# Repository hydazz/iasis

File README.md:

# iasis

Iasis is a five-port USB-C hub for putting Apple Silicon and T2 Macs into DFU mode without the keyboard sequence. A Mac or Linux host runs the restores; Iasis handles the connections, port power and DFU signalling.

The hardware is a prototype.

## Hardware

| Build | Power and connections                                                                        |
| ----- | -------------------------------------------------------------------------------------------- |
| Hub   | Host USB power for the hub, controls and restores from charged targets                       |
| HubPD | Adds a USB-C power input and per-port charging supplies; works as Hub without a power supply |

The optional [CM5 carrier](hardware/boards/cm5/README.md) plugs into HubPD and houses a Compute Module 5, NVMe storage and Ethernet. Both builds fit the [printed case](hardware/case/README.md), with plain or OLED lids.

See the [main board](hardware/boards/iasis/README.md) for fabrication files and ordering settings.

## Build

Install [mise](https://mise.jdx.dev/) and, for hardware work, KiCad 10 with its standard libraries. Run from the repository root:

```sh
mise install
mise run deps
mise run host:build
```

The CLI is `target/release/iasis` and runs on macOS and Linux. Linux needs read/write access to the management USB device.

| Task               | Output                                                      |
| ------------------ | ----------------------------------------------------------- |
| `mise run build`   | CLI, firmware, case STLs, board STEPs and fabrication files |
| `mise run lint`    | Rust, Python, workflow and KiCad checks                     |
| `mise run test`    | Software, placement-conversion and case-fit tests           |
| `mise run preview` | Board and case images                                       |
| `mise run format`  | Formatted sources and configuration                         |

Builds, checks and previews are separate tasks. Python tools share the root `.venv`; `mise install` also installs the Lefthook hooks.

## Use

Connect the host and charged targets. Ports are numbered 1–5, starting at the dot on the case.

```sh
target/release/iasis list
target/release/iasis --serial 0123456789abcdef status
target/release/iasis --serial 0123456789abcdef dfu 1
target/release/iasis --serial 0123456789abcdef ports --watch
```

Use the serial reported by `list`. Wait for a port to reach `Ready` or `Contract` before sending DFU or reboot. `ports --watch` shows USB enumeration and device identity. Add `--device t2` to `dfu` for a T2 Mac.

| Button gesture        | Action on ready ports                   |
| --------------------- | --------------------------------------- |
| Click                 | Apple Silicon DFU                       |
| Hold for 1.2 seconds  | Reboot connected targets                |
| Two clicks, then hold | Request a restore from a listening host |

DFU does not erase a device. You can use the button with Apple Configurator, or run restores with the CLI below. `power <port> off` disables a port; `power <port> on` enables it and retries a fault.

Native USB-C uses the host's advertised current. With a legacy A-to-C connection, set the remaining shared USB allowance, including Iasis and after subtracting other loads:

```sh
target/release/iasis --serial 0123456789abcdef host-budget 1200
```

The [firmware power table](crates/firmware/README.md#port-power) lists the limits.

### Restore

Install [idevicerestore](https://github.com/libimobiledevice/idevicerestore) and its dependencies. Use the system `usbmuxd` service; macOS includes it, while Linux needs it installed and running.

With a local IPSW:

```sh
target/release/iasis ipsw /path/to/UniversalMac.ipsw
target/release/iasis --serial 0123456789abcdef restore /path/to/UniversalMac.ipsw --ports 1,2,3,4,5 --erase
```

**`--erase` erases the selected targets.** To prepare a batch and start it with the button, replace `--ports 1,2,3,4,5` with `--button`. The command waits for a new restore gesture and exits after that batch. Use `--host-ma 1200` to set a legacy host allowance for the batch.

Each target gets its own idevicerestore process, selected by ECID. Logs and working files go under `restores/`, or the directory passed to `--logs`. Allow space for an extracted OS image per worker. Iasis checks the local archive; idevicerestore checks device compatibility and Apple signing.

## Firmware and protocol

[Build, flash and recover the firmware](crates/firmware/README.md) through the same host USB connection. The [protocol README](crates/protocol/README.md) describes the management interface for host applications.

## License

Original code, firmware, CAD, documentation and enclosure files are [Apache-2.0](LICENSE). Third-party assets retain their own licences and notices.

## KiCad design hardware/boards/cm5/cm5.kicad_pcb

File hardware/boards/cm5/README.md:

# CM5 carrier

An optional Raspberry Pi Compute Module 5 carrier for Iasis. It plugs into the main board's HubPD population and carries Ethernet, NVMe storage, an accessory USB-C port and a service USB-C port. The [CM5 case](../../case/README.md#cm5-assembly) holds both boards.

## Parts and power

| Item                      | Requirement or limit                                       |
| ------------------------- | ---------------------------------------------------------- |
| Main board                | HubPD, with its fitted side socket and power feed          |
| Input                     | USB-C PD supply offering 20 V, connected to the main board |
| Storage                   | eMMC on the module, or NVMe for CM5 Lite; no microSD slot  |
| NVMe SSD                  | M-key, 2230 / 2242 / 2280, up to 6 W                       |
| Fan                       | Up to 0.4 A; rated to tolerate 5.19 V                      |
| RTC backup                | Raspberry Pi RTC Battery SC1163, rechargeable ML2020       |
| Accessory USB-C           | 5 V / 1.5 A                                                |
| Carrier power reservation | 35 W including conversion losses and VCONN                 |

The service port is for CM5 provisioning and recovery; power comes through the main board. Set [`PSU_MAX_CURRENT=5000`](https://www.raspberrypi.com/documentation/computers/raspberry-pi.html#PSU_MAX_CURRENT) in the CM5 EEPROM configuration for the accessory USB allowance.

## RTC battery

Connect the battery to J104. To enable charging, add this to `/boot/firmware/config.txt` and reboot:

```ini
dtparam=rtc_bbat_vchg=3000000
```

Use this setting only with the specified rechargeable battery. See [Raspberry Pi's RTC setup](https://www.raspberrypi.com/documentation/computers/raspberry-pi.html#enable-battery-charging) for diagnostics.

## Fabrication

With the [development tools](../../../README.md#build) installed:

```sh
mise run //hardware/boards/cm5:lint
mise run //hardware/boards/cm5:fab
```

`build/boards/cm5/` contains `gerbers.zip`, `bom.csv` and `cpl.csv`. The board is 75.1 × 102 mm and uses the [main board's six-layer ordering settings](../iasis/README.md#jlcpcb-order). Select its accessory and service USB-C connectors (`J401`, `J501`) in the assembly order.

Use `:step` for the populated STEP and `:preview` for `board.png`. The PCB revision is recorded in the KiCad title block; tag Revision A fabrication files as `cm5-rev-a`.

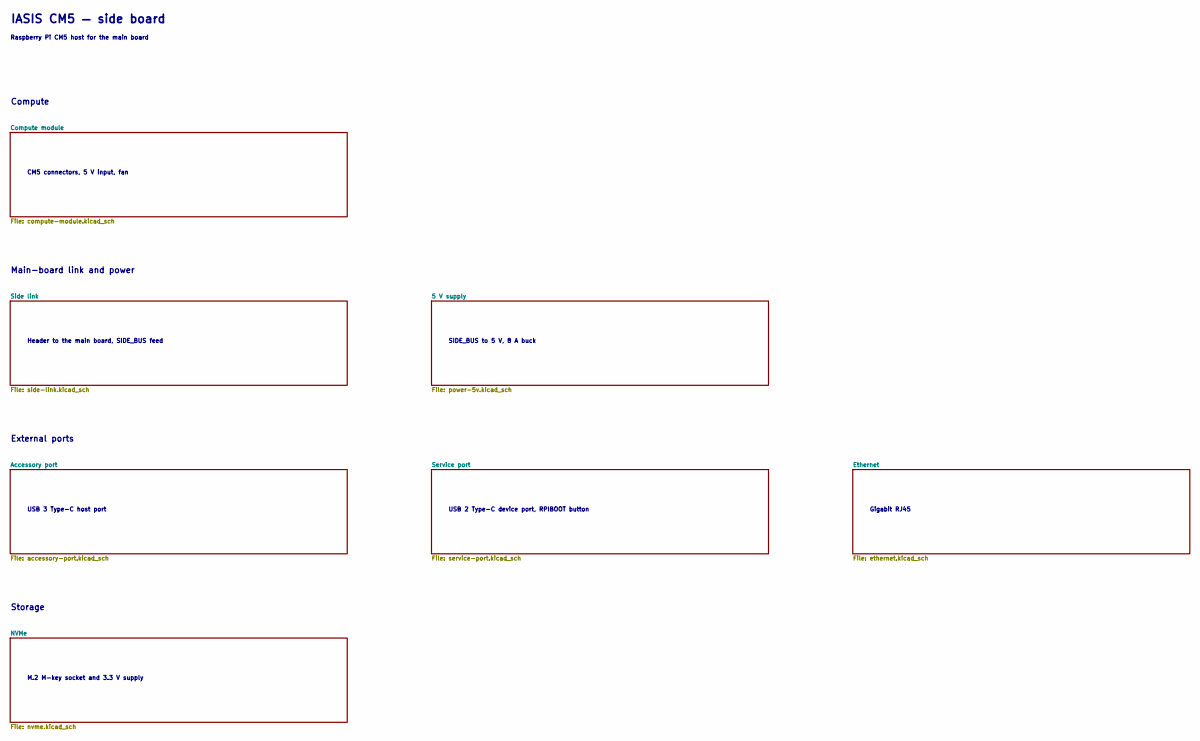
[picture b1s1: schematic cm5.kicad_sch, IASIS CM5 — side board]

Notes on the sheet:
Compute
CM5 connectors, 5 V input, fan
Main-board link and power
Header to the main board, SIDE_BUS feed
SIDE_BUS to 5 V, 8 A buck
External ports
USB 3 Type-C host port
USB 2 Type-C device port, RPIBOOT button
Gigabit RJ45
Storage
M.2 M-key socket and 3.3 V supply
IASIS CM5 — side board
Raspberry Pi CM5 host for the main board

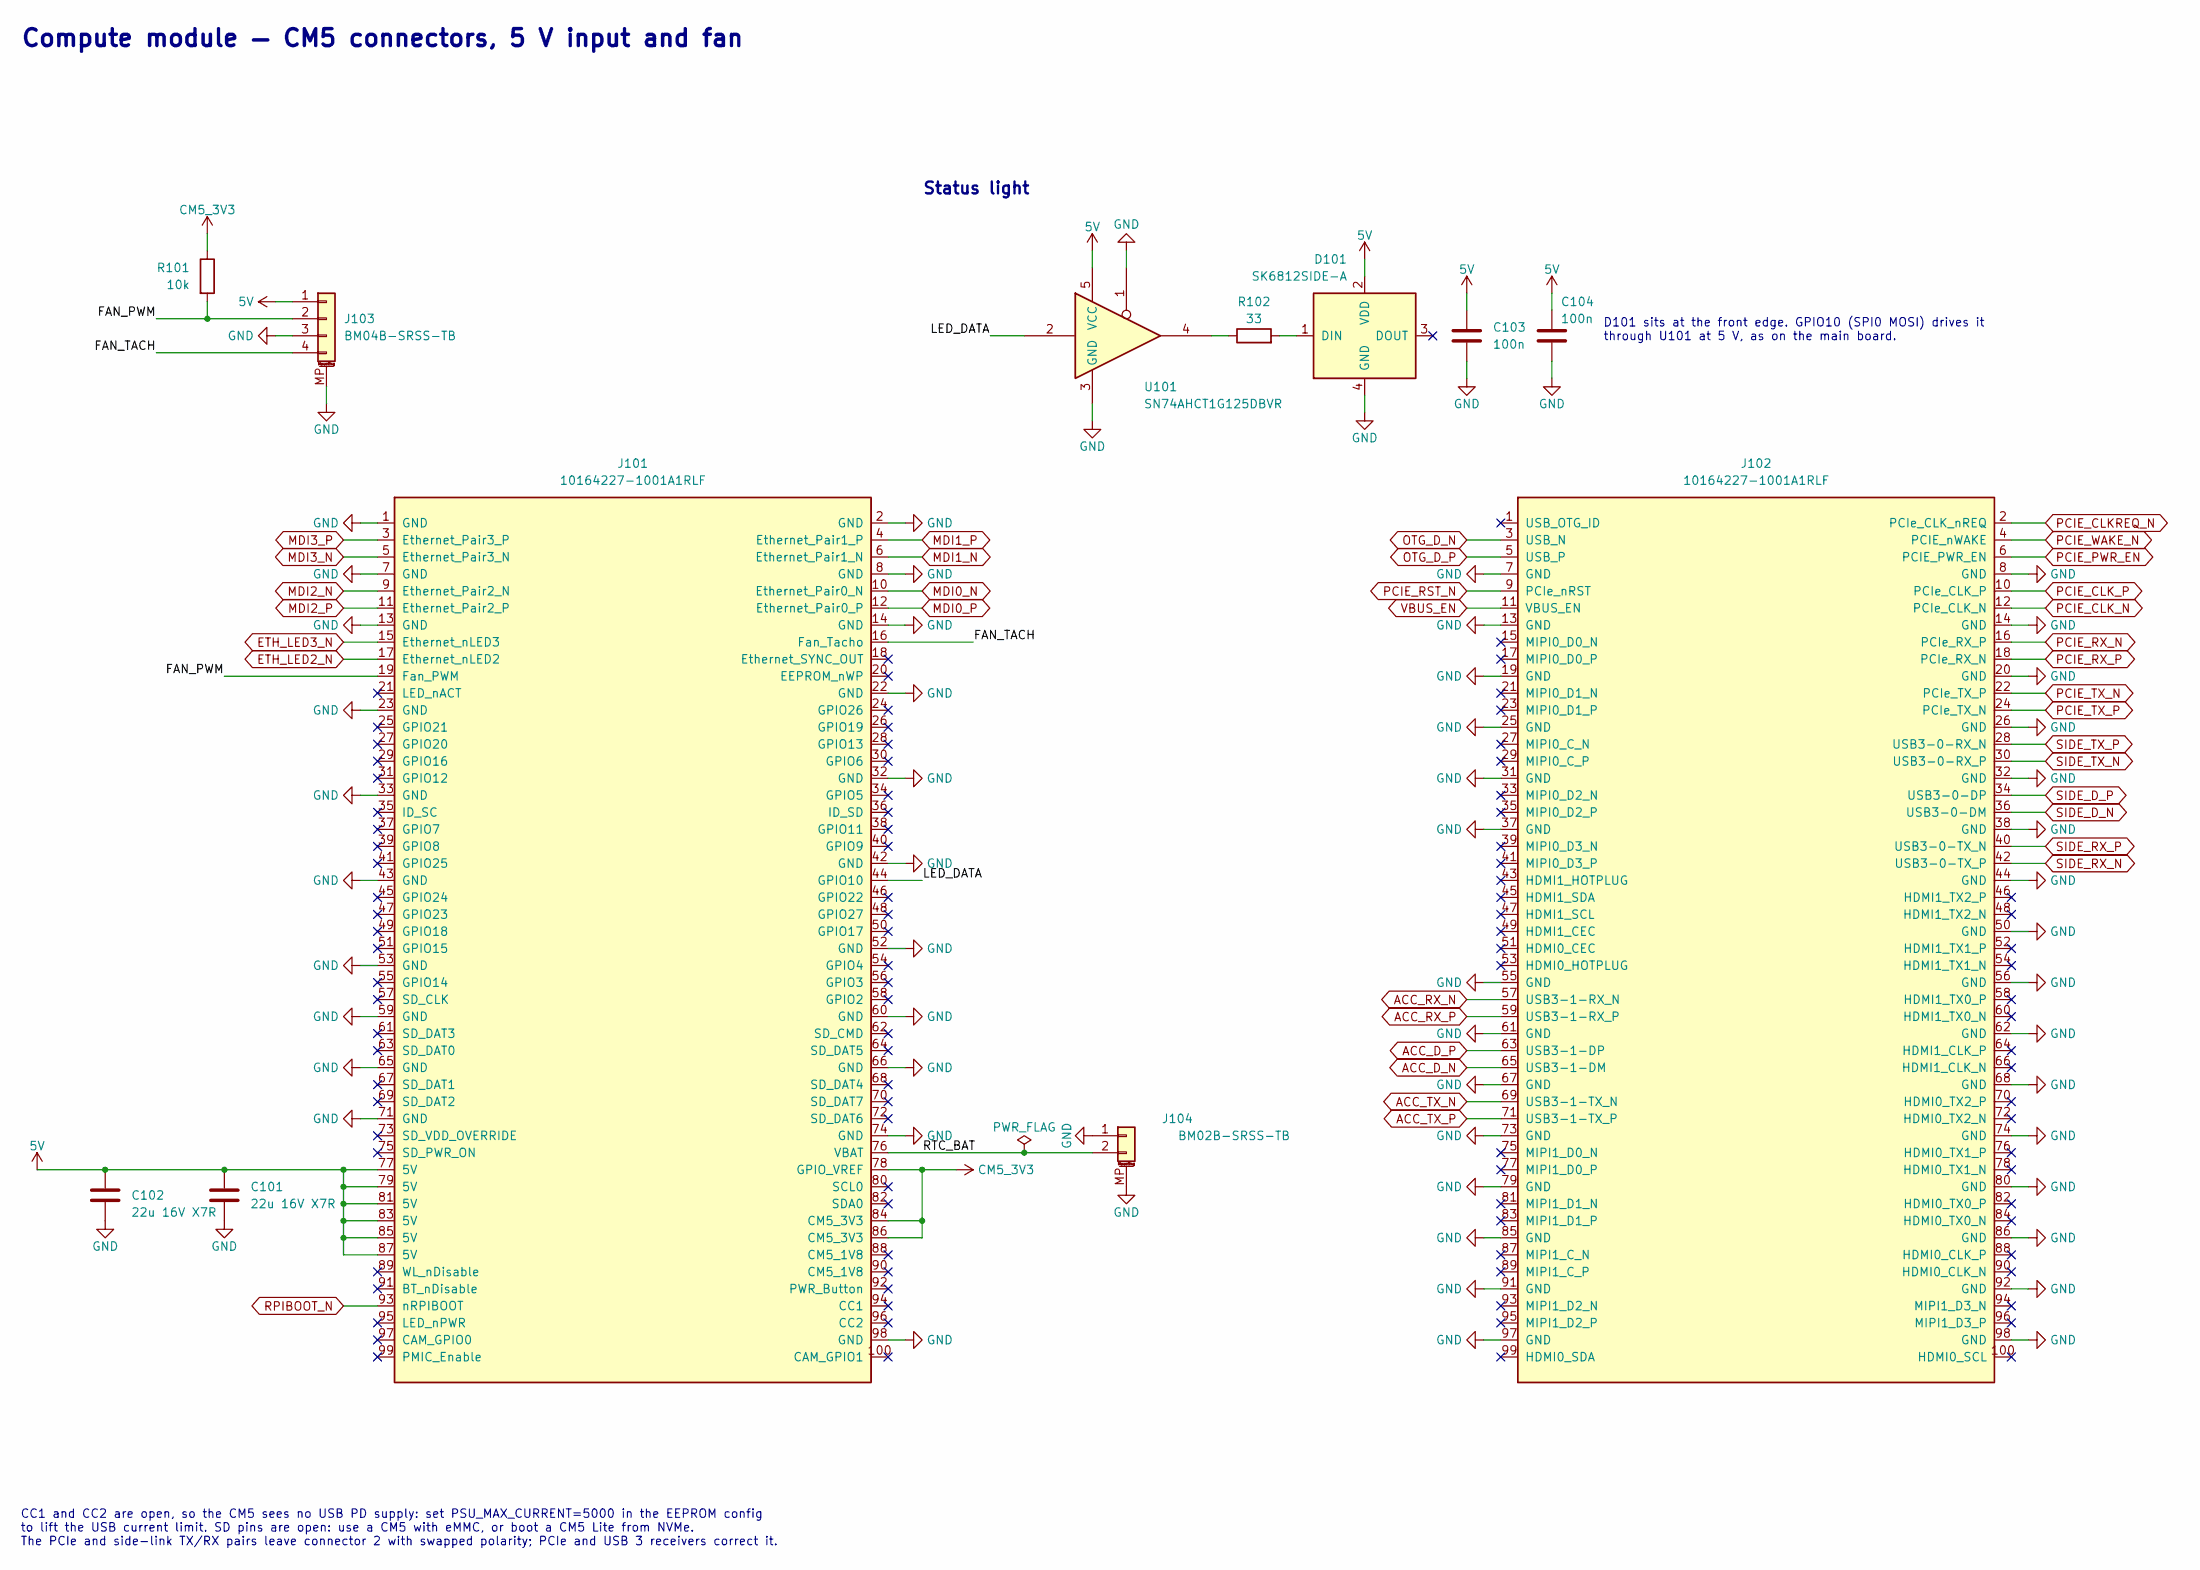
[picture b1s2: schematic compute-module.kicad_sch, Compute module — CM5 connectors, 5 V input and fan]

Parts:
C101, C102: 22u 16V X7R; C_1210_3225Metric; MPN CL32B226KOJNNNE; LCSC C55530
C103, C104: 100n; C_0402_1005Metric; MPN CL05B104KO5NNNC; LCSC C1525
D101: SK6812SIDE-A; OPSCO_SK6812SIDE-A; MPN SK6812SIDE-A; LCSC C5378721
J101, J102: 10164227-1001A1RLF; Hirose_DF40C-100DS-0.4V_2x50_P0.4mm; MPN 10164227-1001A1RLF; LCSC C6782225
J103: BM04B-SRSS-TB; JST_SH_BM04B-SRSS-TB_1x04-1MP_P1.00mm_Vertical; MPN BM04B-SRSS-TB(LF)(SN); LCSC C160390
J104: BM02B-SRSS-TB; JST_SH_BM02B-SRSS-TB_1x02-1MP_P1.00mm_Vertical; MPN BM02B-SRSS-TB(LF)(SN); LCSC C160388
R101: 10k; R_0402_1005Metric; MPN 0402WGF1002TCE; LCSC C25744
R102: 33; R_0402_1005Metric; MPN 0402WGF330JTCE; LCSC C25105
U101: SN74AHCT1G125DBVR; SOT-23-5; MPN SN74AHCT1G125DBVR; LCSC C7484

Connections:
5V: C101.1, C102.1, C103.1, C104.1, D101.2 (VDD), J101.77 (5V), J101.79 (5V), J101.81 (5V), J101.83 (5V), J101.85 (5V), J101.87 (5V), J103.1, U101.5 (VCC); also elsewhere on the board
/Compute module/FAN_PWM: J101.19 (Fan_PWM), J103.2, R101.2
/Compute module/FAN_TACH: J101.16 (Fan_Tacho), J103.4
/Compute module/LED_DATA: J101.44 (GPIO10), U101.2
/Compute module/RTC_BAT: J101.76 (VBAT), J104.2
ACC_D_N: J102.65 (USB3-1-DM); also elsewhere on the board
ACC_D_P: J102.63 (USB3-1-DP); also elsewhere on the board
ACC_RX_N: J102.57 (USB3-1-RX_N); also elsewhere on the board
ACC_RX_P: J102.59 (USB3-1-RX_P); also elsewhere on the board
ACC_TX_N: J102.69 (USB3-1-TX_N); also elsewhere on the board
ACC_TX_P: J102.71 (USB3-1-TX_P); also elsewhere on the board
CM5_3V3: J101.78 (GPIO_VREF), J101.84 (CM5_3V3), J101.86 (CM5_3V3), R101.1; also elsewhere on the board
ETH_LED2_N: J101.17 (Ethernet_nLED2); also elsewhere on the board
ETH_LED3_N: J101.15 (Ethernet_nLED3); also elsewhere on the board
GND: C101.2, C102.2, C103.2, C104.2, D101.4 (GND), J101.1 (GND), J101.2 (GND), J101.7 (GND), J101.8 (GND), J101.13 (GND), J101.14 (GND), J101.22 (GND), J101.23 (GND), J101.32 (GND), J101.33 (GND), J101.42 (GND), J101.43 (GND), J101.52 (GND), J101.53 (GND), J101.59 (GND), J101.60 (GND), J101.65 (GND), J101.66 (GND), J101.71 (GND), J101.74 (GND), J101.98 (GND), J102.7 (GND), J102.8 (GND), J102.13 (GND), J102.14 (GND), J102.19 (GND), J102.20 (GND), J102.25 (GND), J102.26 (GND), J102.31 (GND), J102.32 (GND), J102.37 (GND), J102.38 (GND), J102.44 (GND), J102.50 (GND), J102.55 (GND), J102.56 (GND), J102.61 (GND), J102.62 (GND), J102.67 (GND), J102.68 (GND), J102.73 (GND), J102.74 (GND), J102.79 (GND), J102.80 (GND), J102.85 (GND), J102.86 (GND), J102.91 (GND), J102.92 (GND), J102.97 (GND), J102.98 (GND), J103.3, J103.MP (MountPin), J104.1, J104.MP (MountPin), U101.1, U101.3 (GND); also elsewhere on the board
MDI0_N: J101.10 (Ethernet_Pair0_N); also elsewhere on the board
MDI0_P: J101.12 (Ethernet_Pair0_P); also elsewhere on the board
MDI1_N: J101.6 (Ethernet_Pair1_N); also elsewhere on the board
MDI1_P: J101.4 (Ethernet_Pair1_P); also elsewhere on the board
MDI2_N: J101.9 (Ethernet_Pair2_N); also elsewhere on the board
MDI2_P: J101.11 (Ethernet_Pair2_P); also elsewhere on the board
MDI3_N: J101.5 (Ethernet_Pair3_N); also elsewhere on the board
MDI3_P: J101.3 (Ethernet_Pair3_P); also elsewhere on the board
unnamed: D101.1 (DIN), R102.2
unnamed: R102.1, U101.4
OTG_D_N: J102.3 (USB_N); also elsewhere on the board
OTG_D_P: J102.5 (USB_P); also elsewhere on the board
PCIE_CLKREQ_N: J102.2 (PCIe_CLK_nREQ); also elsewhere on the board
PCIE_CLK_N: J102.12 (PCIe_CLK_N); also elsewhere on the board
PCIE_CLK_P: J102.10 (PCIe_CLK_P); also elsewhere on the board
PCIE_PWR_EN: J102.6 (PCIE_PWR_EN); also elsewhere on the board
PCIE_RST_N: J102.9 (PCIe_nRST); also elsewhere on the board
PCIE_RX_N: J102.16 (PCIe_RX_P); also elsewhere on the board
PCIE_RX_P: J102.18 (PCIe_RX_N); also elsewhere on the board
PCIE_TX_N: J102.22 (PCIe_TX_P); also elsewhere on the board
PCIE_TX_P: J102.24 (PCIe_TX_N); also elsewhere on the board
PCIE_WAKE_N: J102.4 (PCIE_nWAKE); also elsewhere on the board
RPIBOOT_N: J101.93 (nRPIBOOT); also elsewhere on the board
SIDE_D_N: J102.36 (USB3-0-DM); also elsewhere on the board
SIDE_D_P: J102.34 (USB3-0-DP); also elsewhere on the board
SIDE_RX_N: J102.42 (USB3-0-TX_P); also elsewhere on the board
SIDE_RX_P: J102.40 (USB3-0-TX_N); also elsewhere on the board
SIDE_TX_N: J102.30 (USB3-0-RX_P); also elsewhere on the board
SIDE_TX_P: J102.28 (USB3-0-RX_N); also elsewhere on the board
VBUS_EN: J102.11 (VBUS_EN); also elsewhere on the board

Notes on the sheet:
Compute module — CM5 connectors, 5 V input and fan
CC1 and CC2 are open, so the CM5 sees no USB PD supply: set PSU_MAX_CURRENT=5000 in the EEPROM config to lift the USB current limit. SD pins are open: use a CM5 with eMMC, or boot a CM5 Lite from NVMe. The PCIe and side-link TX/RX pairs leave connector 2 with swapped polarity; PCIe and USB 3 receiv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
Status light
D101 sits at the front edge. GPIO10 (SPI0 MOSI) drives it through U101 at 5 V, as on the main board.

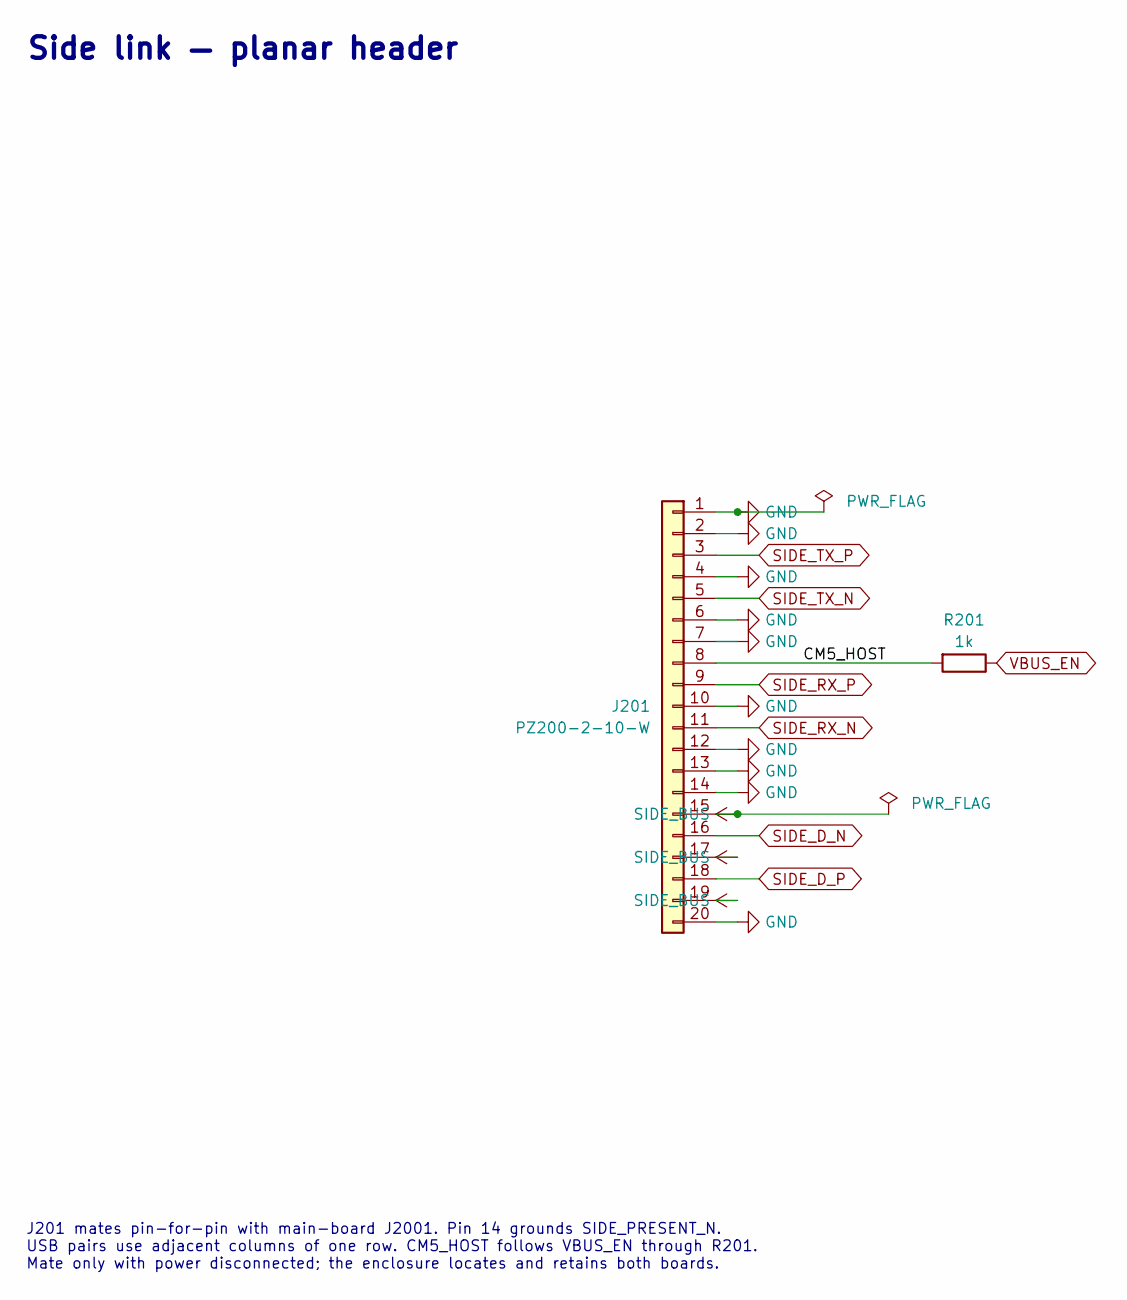
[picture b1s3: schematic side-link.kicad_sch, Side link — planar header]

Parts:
J201: PZ200-2-10-W; PinHeader_2x10_P2.00mm_Horizontal; MPN PZ200-2-10-W; LCSC C2906016
R201: 1k; R_0402_1005Metric; MPN 0402WGF1001TCE; LCSC C11702

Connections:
/Side link/CM5_HOST: J201.8, R201.2
GND: J201.1, J201.2, J201.4, J201.6, J201.7, J201.10, J201.12, J201.13, J201.14, J201.20; also elsewhere on the board
SIDE_BUS: J201.15, J201.17, J201.19; also elsewhere on the board
SIDE_D_N: J201.16; also elsewhere on the board
SIDE_D_P: J201.18; also elsewhere on the board
SIDE_RX_N: J201.11; also elsewhere on the board
SIDE_RX_P: J201.9; also elsewhere on the board
SIDE_TX_N: J201.5; also elsewhere on the board
SIDE_TX_P: J201.3; also elsewhere on the board
VBUS_EN: R201.1; also elsewhere on the board

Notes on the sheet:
Side link — planar header
J201 mates pin-for-pin with main-board J2001. Pin 14 grounds SIDE_PRESENT_N. USB pairs use adjacent columns of one row. CM5_HOST follows VBUS_EN through R201. Mate only with power disconnected; the enclosure locates and retains both boards.

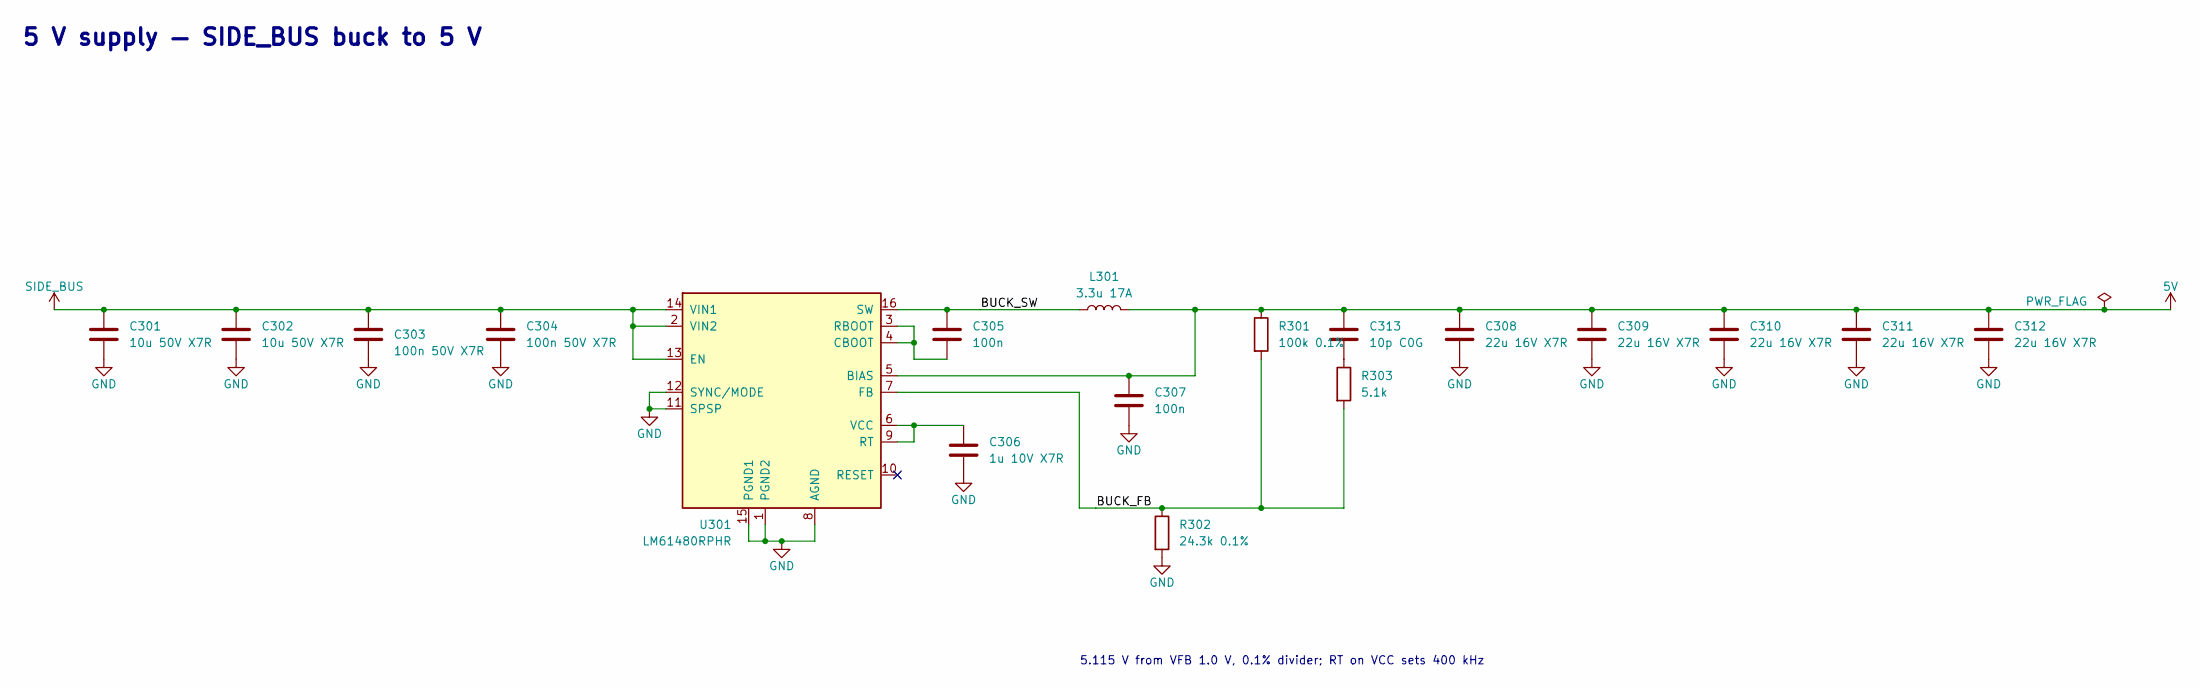
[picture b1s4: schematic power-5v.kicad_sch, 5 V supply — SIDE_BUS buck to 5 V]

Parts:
C301, C302: 10u 50V X7R; C_1210_3225Metric; MPN CL32B106KBJNNNE; LCSC C138687
C303, C304: 100n 50V X7R; C_0402_1005Metric; MPN CL05B104KB54PNC; LCSC C307331
C305, C307: 100n; C_0402_1005Metric; MPN CL05B104KO5NNNC; LCSC C1525
C306: 1u 10V X7R; C_0603_1608Metric; MPN CGA0603X7R105K100JT; LCSC C22399625
C308, C309, C310, C311, C312: 22u 16V X7R; C_1210_3225Metric; MPN CL32B226KOJNNNE; LCSC C55530
C313: 10p C0G; C_0402_1005Metric; MPN CL05C100JB5NNNC; LCSC C32949
L301: 3.3u 17A; L_PROD_PSPMAA0805; MPN PSPMAA0805-3R3M-ANP; LCSC C2962881
R301: 100k 0.1%; R_0402_1005Metric; MPN ARG02BTC1003; LCSC C2984406
R302: 24.3k 0.1%; R_0402_1005Metric; MPN ARG02BTC2432; LCSC C2681592
R303: 5.1k; R_0402_1005Metric; MPN 0402WGF5101TCE; LCSC C25905
U301: LM61480RPHR; TI_RPH0016A; MPN LM61480RPHR; LCSC C3198089

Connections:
5V: C307.1, C308.1, C309.1, C310.1, C311.1, C312.1, C313.1, L301.2, R301.1, U301.5 (BIAS); also elsewhere on the board
/5 V supply/BUCK_FB: R301.2, R302.1, R303.2, U301.7 (FB)
/5 V supply/BUCK_SW: C305.1, L301.1, U301.16 (SW)
GND: C301.2, C302.2, C303.2, C304.2, C306.2, C307.2, C308.2, C309.2, C310.2, C311.2, C312.2, R302.2, U301.1 (PGND2), U301.8 (AGND), U301.11 (SPSP), U301.12 (SYNC/MODE), U301.15 (PGND1); also elsewhere on the board
unnamed: C313.2, R303.1
unnamed: C305.2, U301.3 (RBOOT), U301.4 (CBOOT)
unnamed: C306.1, U301.6 (VCC), U301.9 (RT)
SIDE_BUS: C301.1, C302.1, C303.1, C304.1, U301.2 (VIN2), U301.13 (EN), U301.14 (VIN1); also elsewhere on the board

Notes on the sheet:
5 V supply — SIDE_BUS buck to 5 V
5.115 V from VFB 1.0 V, 0.1% divider; RT on VCC sets 400 kHz

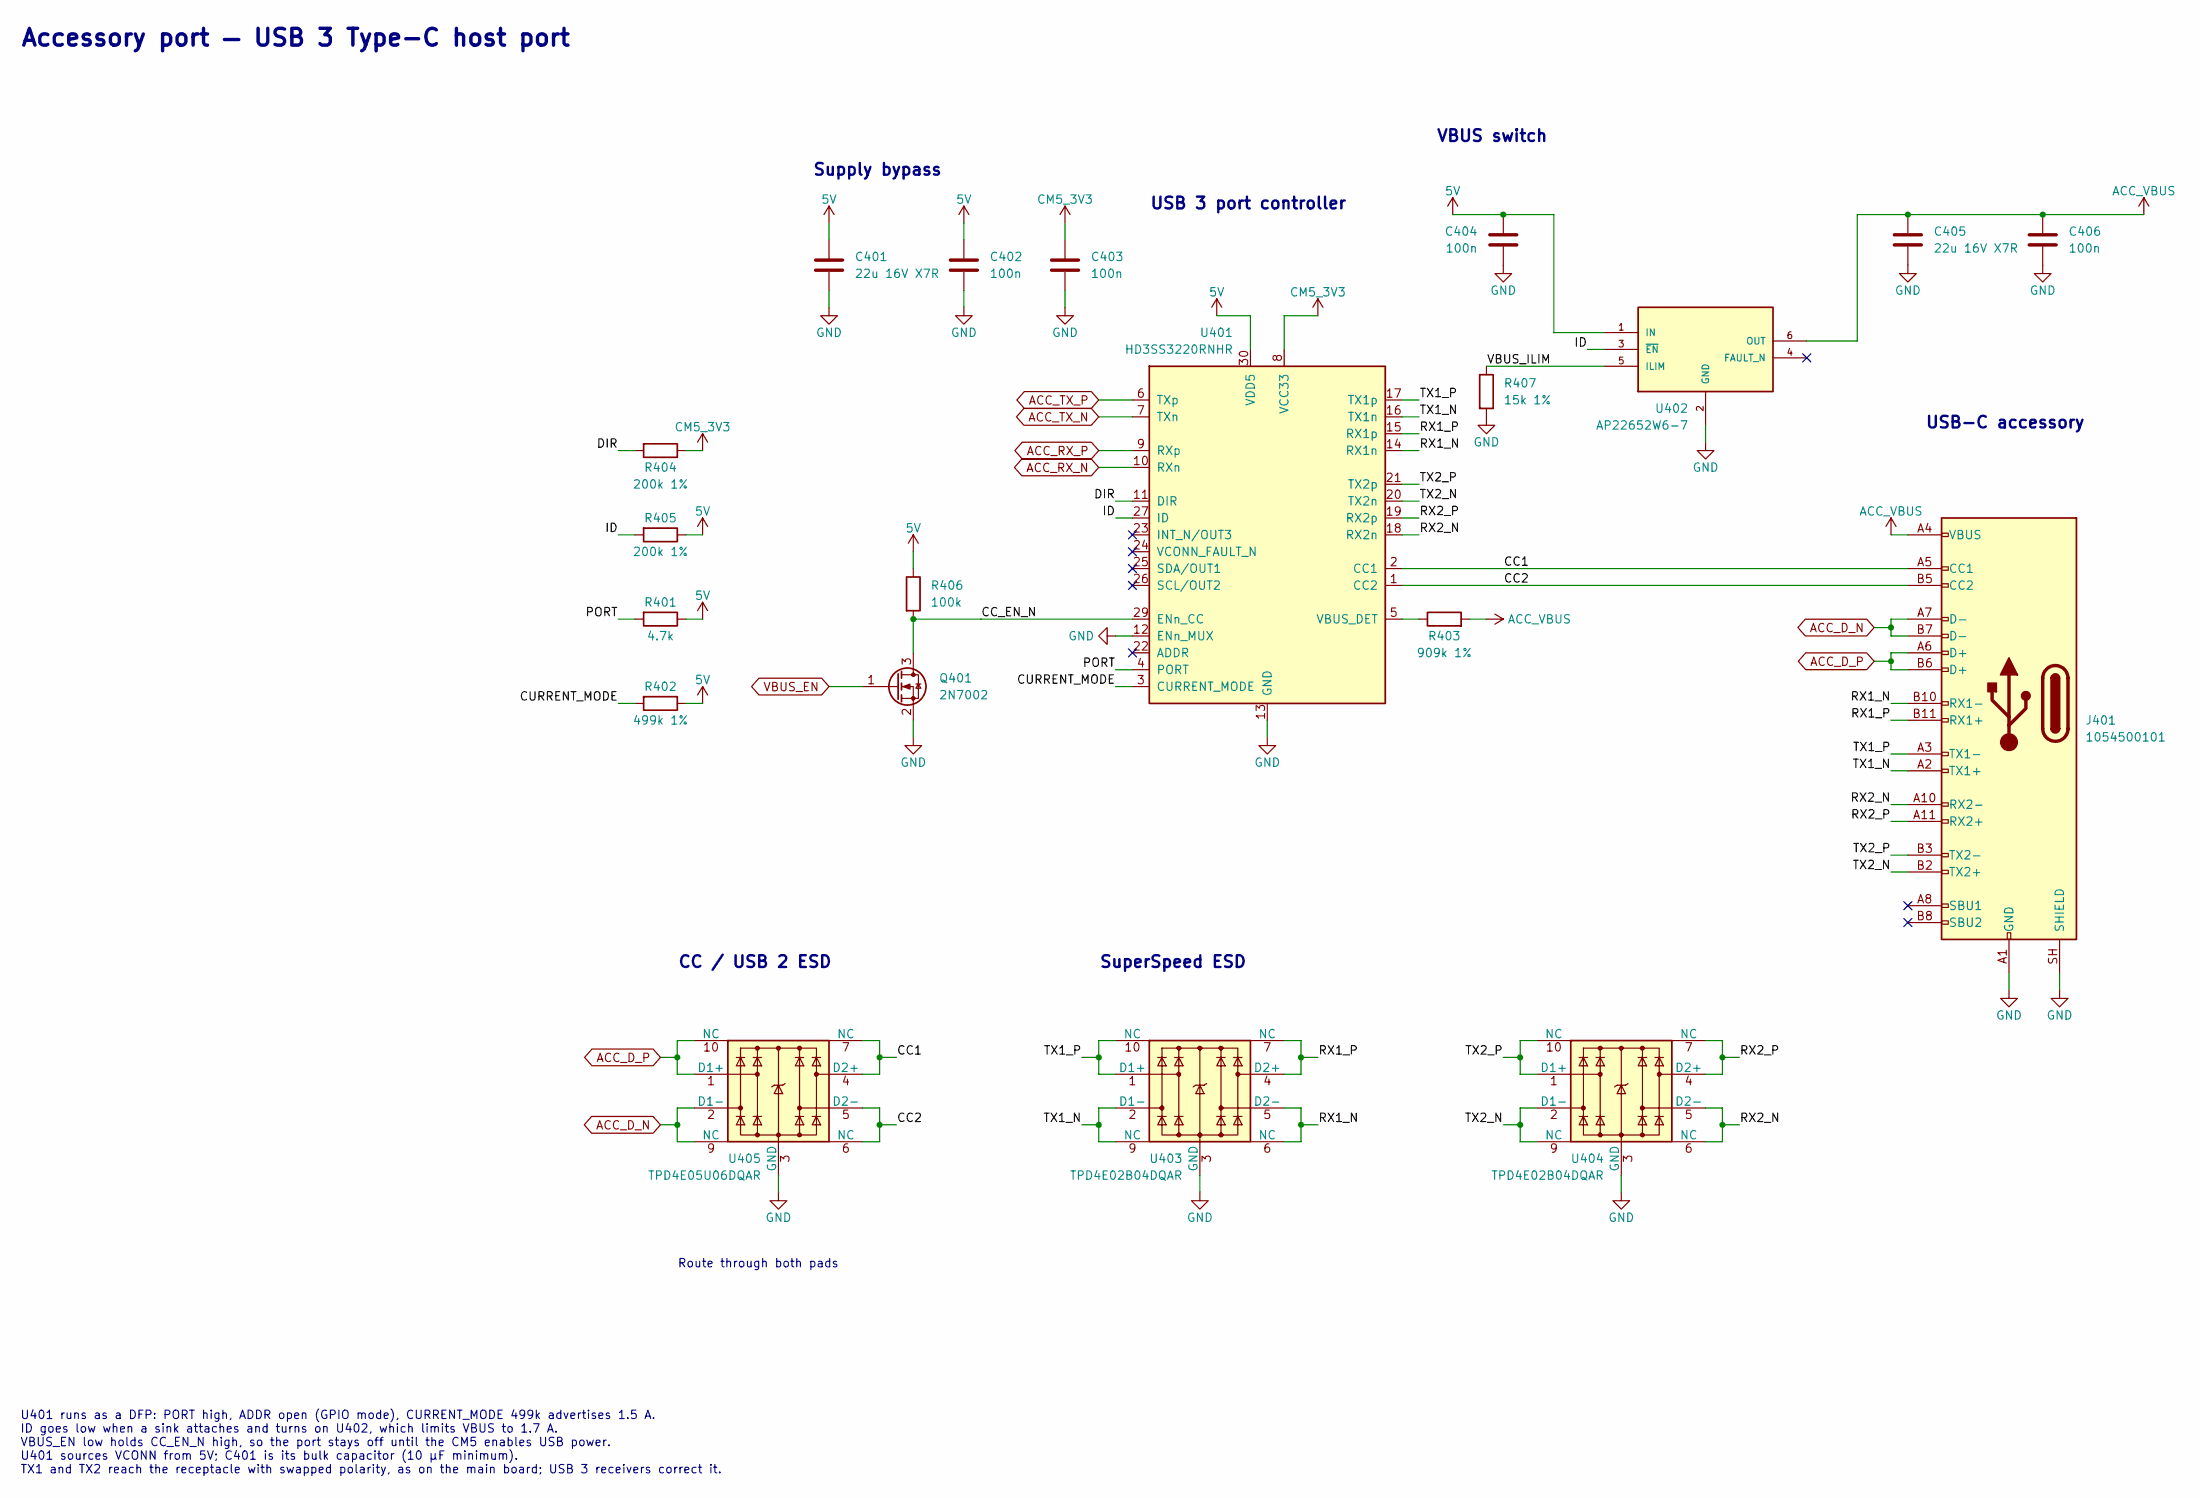
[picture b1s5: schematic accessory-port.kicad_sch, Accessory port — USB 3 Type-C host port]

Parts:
C401, C405: 22u 16V X7R; C_1210_3225Metric; MPN CL32B226KOJNNNE; LCSC C55530
C402, C403, C404, C406: 100n; C_0402_1005Metric; MPN CL05B104KO5NNNC; LCSC C1525
J401: 1054500101; USB_C_Receptacle_Molex_105450-0101; MPN 1054500101; LCSC C134092
Q401: 2N7002; SOT-23; MPN 2N7002; LCSC C8545
R401: 4.7k; R_0402_1005Metric; MPN 0402WGF4701TCE; LCSC C25900
R402: 499k 1%; R_0402_1005Metric; MPN 0402WGF4993TCE; LCSC C25793
R403: 909k 1%; R_0402_1005Metric; MPN 0402WGF9093TCE; LCSC C25799
R404, R405: 200k 1%; R_0402_1005Metric; MPN 0402WGF2003TCE; LCSC C25764
R406: 100k; R_0402_1005Metric; MPN 0402WGF1003TCE; LCSC C25741
R407: 15k 1%; R_0402_1005Metric; MPN 0402WGF1502TCE; LCSC C25756
U401: HD3SS3220RNHR; Texas_RNH0030A_WQFN-30-1EP_2.5x4.5mm_P0.4mm_EP1.2x3.2mm; MPN HD3SS3220RNHR; LCSC C165155
U402: AP22652W6-7; SOT-23-6; MPN AP22652W6-7; LCSC C2158038
U403, U404: TPD4E02B04DQAR; USON-10_2.5x1.0mm_P0.5mm; MPN TPD4E02B04DQAR; LCSC C106794
U405: TPD4E05U06DQAR; USON-10_2.5x1.0mm_P0.5mm; MPN TPD4E05U06DQAR; LCSC C138714

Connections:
5V: C401.1, C402.1, C404.1, R401.1, R402.1, R405.1, R406.1, U401.30 (VDD5), U402.1 (IN); also elsewhere on the board
/Accessory port/CC1: J401.A5 (CC1), U401.2 (CC1), U405.4 (D2+), U405.7 (NC)
/Accessory port/CC2: J401.B5 (CC2), U401.1 (CC2), U405.5 (D2-), U405.6 (NC)
/Accessory port/CC_EN_N: Q401.3 (D), R406.2, U401.29 (ENn_CC)
/Accessory port/CURRENT_MODE: R402.2, U401.3 (CURRENT_MODE)
/Accessory port/DIR: R404.2, U401.11 (DIR)
/Accessory port/ID: R405.2, U401.27 (ID), U402.3 (~EN)
/Accessory port/PORT: R401.2, U401.4 (PORT)
/Accessory port/RX1_N: J401.B10 (RX1-), U401.14 (RX1n), U403.5 (D2-), U403.6 (NC)
/Accessory port/RX1_P: J401.B11 (RX1+), U401.15 (RX1p), U403.4 (D2+), U403.7 (NC)
/Accessory port/RX2_N: J401.A10 (RX2-), U401.18 (RX2n), U404.5 (D2-), U404.6 (NC)
/Accessory port/RX2_P: J401.A11 (RX2+), U401.19 (RX2p), U404.4 (D2+), U404.7 (NC)
/Accessory port/TX1_N: J401.A2 (TX1+), U401.16 (TX1n), U403.2 (D1-), U403.9 (NC)
/Accessory port/TX1_P: J401.A3 (TX1-), U401.17 (TX1p), U403.1 (D1+), U403.10 (NC)
/Accessory port/TX2_N: J401.B2 (TX2+), U401.20 (TX2n), U404.2 (D1-), U404.9 (NC)
/Accessory port/TX2_P: J401.B3 (TX2-), U401.21 (TX2p), U404.1 (D1+), U404.10 (NC)
/Accessory port/VBUS_ILIM: R407.1, U402.5 (ILIM)
ACC_D_N: J401.A7 (D-), J401.B7 (D-), U405.2 (D1-), U405.9 (NC); also elsewhere on the board
ACC_D_P: J401.A6 (D+), J401.B6 (D+), U405.1 (D1+), U405.10 (NC); also elsewhere on the board
ACC_RX_N: U401.10 (RXn); also elsewhere on the board
ACC_RX_P: U401.9 (RXp); also elsewhere on the board
ACC_TX_N: U401.7 (TXn); also elsewhere on the board
ACC_TX_P: U401.6 (TXp); also elsewhere on the board
ACC_VBUS: C405.1, C406.1, J401.A4 (VBUS), J401.A9 (VBUS), J401.B4 (VBUS), J401.B9 (VBUS), R403.2, U402.6 (OUT)
CM5_3V3: C403.1, R404.1, U401.8 (VCC33); also elsewhere on the board
GND: C401.2, C402.2, C403.2, C404.2, C405.2, C406.2, J401.A1 (GND), J401.A12 (GND), J401.B1 (GND), J401.B12 (GND), J401.SH (SHIELD), Q401.2 (S), R407.2, U401.12 (ENn_MUX), U401.13 (GND), U401.28 (GND), U401.31 (GND), U402.2 (GND), U403.3 (GND), U403.8 (GND), U404.3 (GND), U404.8 (GND), U405.3 (GND), U405.8 (GND); also elsewhere on the board
unnamed: R403.1, U401.5 (VBUS_DET)
VBUS_EN: Q401.1 (G); also elsewhere on the board

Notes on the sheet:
Accessory port — USB 3 Type-C host port
Supply bypass
USB 3 port controller
VBUS switch
USB-C accessory
CC / USB 2 ESD
SuperSpeed ESD
Route through both pads
U401 runs as a DFP: PORT high, ADDR open (GPIO mode), CURRENT_MODE 499k advertises 1.5 A. ID goes low when a sink attaches and turns on U402, which limits VBUS to 1.7 A. VBUS_EN low holds CC_EN_N high, so the port stays off until the CM5 enables USB power. U401 sources VCONN from 5V; C401 is its bu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

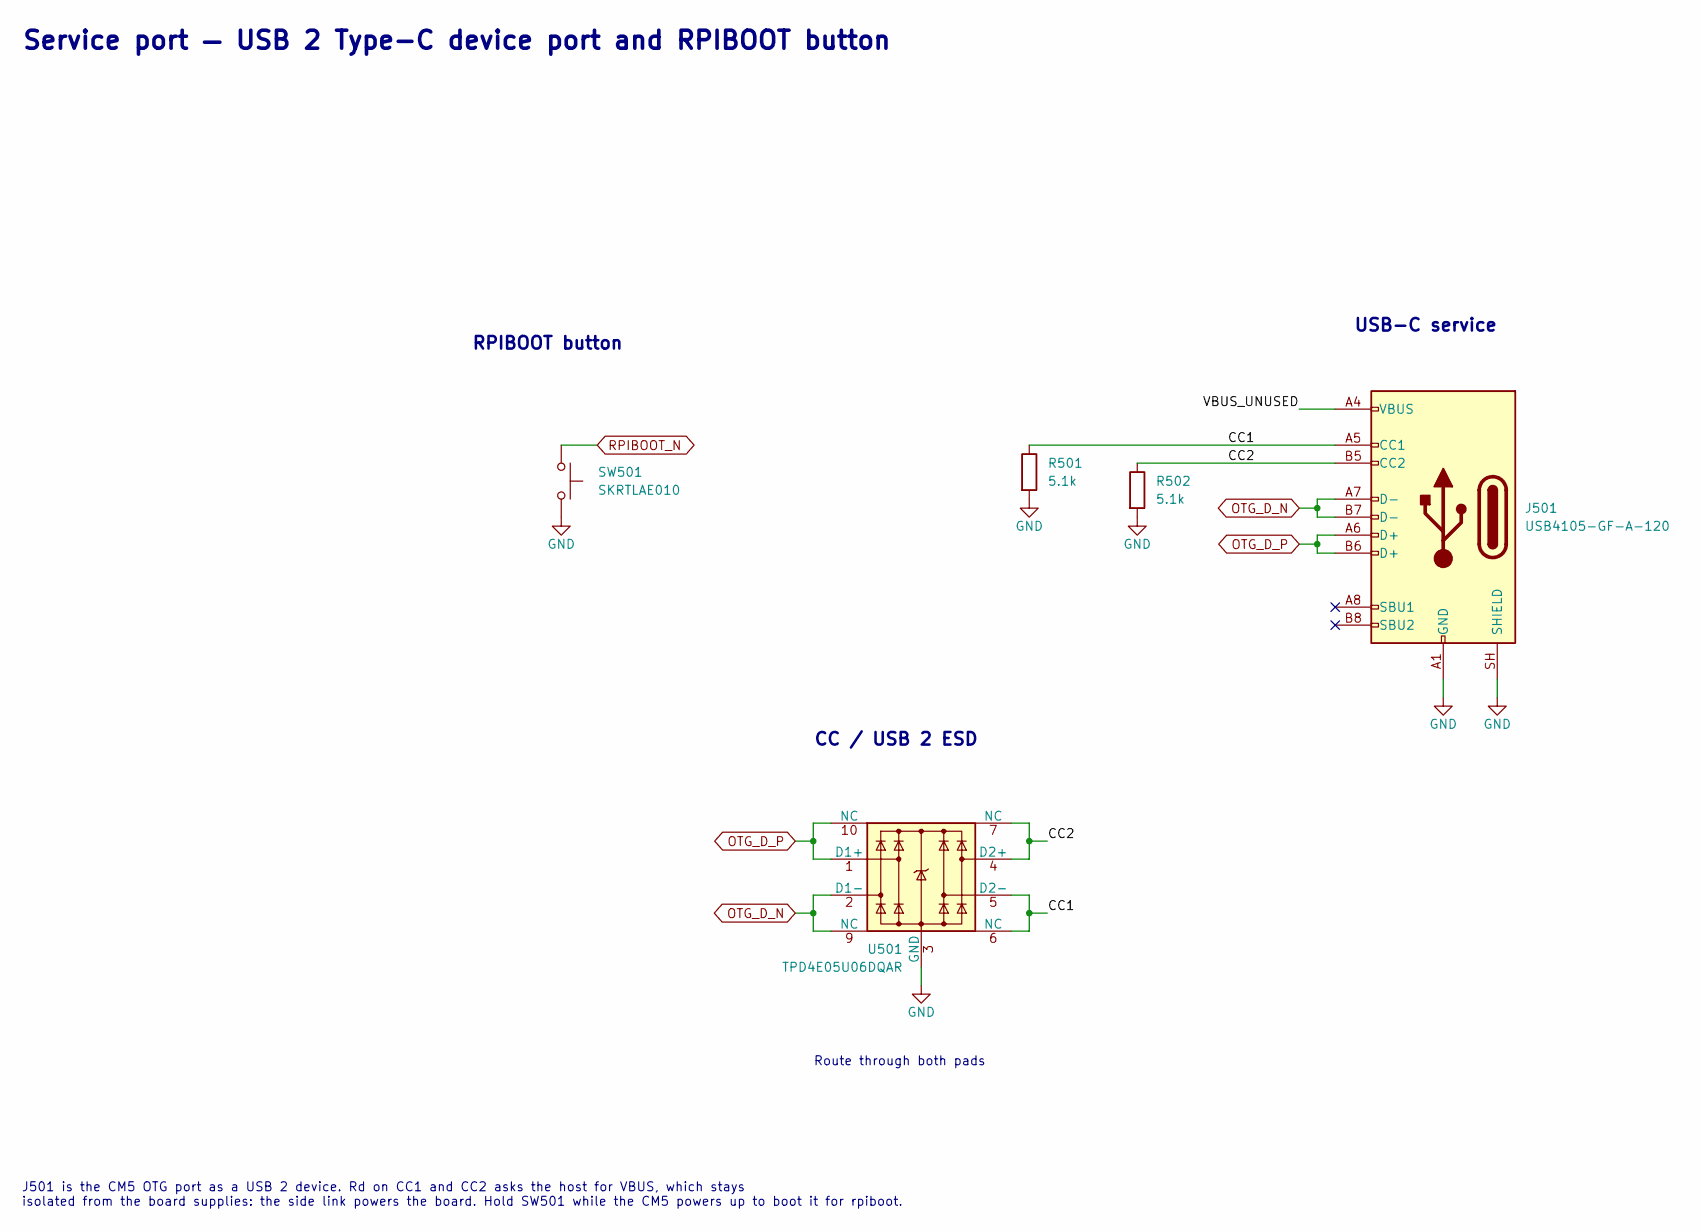
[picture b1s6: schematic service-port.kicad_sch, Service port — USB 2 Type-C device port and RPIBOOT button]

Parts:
J501: USB4105-GF-A-120; GCT_USB4105_GF_A_120; MPN USB4105-GF-A-120; LCSC C5184243
R501, R502: 5.1k; R_0402_1005Metric; MPN 0402WGF5101TCE; LCSC C25905
SW501: SKRTLAE010; SW_Push_1P1T-MP_NO_Horizontal_Alps_SKRTLAE010; MPN SKRTLAE010; LCSC C110293
U501: TPD4E05U06DQAR; USON-10_2.5x1.0mm_P0.5mm; MPN TPD4E05U06DQAR; LCSC C138714

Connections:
/Service port/CC1: J501.A5 (CC1), R501.1, U501.5 (D2-), U501.6 (NC)
/Service port/CC2: J501.B5 (CC2), R502.1, U501.4 (D2+), U501.7 (NC)
/Service port/VBUS_UNUSED: J501.A4 (VBUS), J501.A9 (VBUS), J501.B4 (VBUS), J501.B9 (VBUS)
GND: J501.A1 (GND), J501.A12 (GND), J501.B1 (GND), J501.B12 (GND), J501.SH (SHIELD), R501.2, R502.2, SW501.2, U501.3 (GND), U501.8 (GND); also elsewhere on the board
OTG_D_N: J501.A7 (D-), J501.B7 (D-), U501.2 (D1-), U501.9 (NC); also elsewhere on the board
OTG_D_P: J501.A6 (D+), J501.B6 (D+), U501.1 (D1+), U501.10 (NC); also elsewhere on the board
RPIBOOT_N: SW501.1; also elsewhere on the board

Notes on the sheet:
Route through both pads
USB-C service
CC / USB 2 ESD
RPIBOOT button
J501 is the CM5 OTG port as a USB 2 device. Rd on CC1 and CC2 asks the host for VBUS, which stays isolated from the board supplies: the side link powers the board. Hold SW501 while the CM5 powers up to boot it for rpiboot.
Service port — USB 2 Type-C device port and RPIBOOT button
